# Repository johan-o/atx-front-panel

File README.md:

# atx-front-panel
A simple KiCad project to provide buttons and indicator LEDs for a standard ATX motherboard front header.

## BOM / Parts List

| Count | Part |
| --- | --- |
| 2 | 6x5mm through-hole push buttons |
| 2 | 0805 SMD LEDs |
| 1 | 2x5 2.54 vertical pin header, male | 
| 1 | 2x5 2.54 vertical pin header, female |

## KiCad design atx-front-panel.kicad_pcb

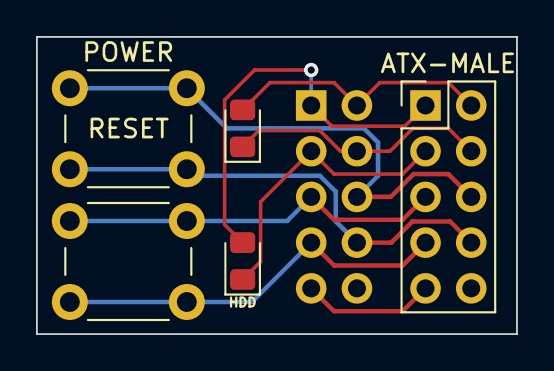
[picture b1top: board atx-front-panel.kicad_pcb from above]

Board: 2 copper layers, 26.7 x 16.5 mm, 6 parts (1 on the bottom side), 9 nets.

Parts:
ATX-FEMALE: Header_02x05_Odd_Even; PinSocket_2x05_P2.54mm_Vertical
ATX-MALE: Conn_02x05_Odd_Even; PinHeader_2x05_P2.54mm_Vertical
DPWR1: LED; LED_0805_2012Metric_Pad1.15x1.40mm_HandSolder
HDD: LED; LED_0805_2012Metric_Pad1.15x1.40mm_HandSolder
POWER: SW_Push; SW_PUSH_6mm_H5mm
RESET: SW_Push; SW_PUSH_6mm_H5mm

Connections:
/HDD_LED+: ATX-FEMALE.1, ATX-MALE.1, HDD.2 (A)
/HDD_LED-: ATX-FEMALE.3, ATX-MALE.3, HDD.1 (K)
/PWR_BUTT1: ATX-FEMALE.6, ATX-MALE.6, POWER.1
/PWR_BUTT2: ATX-FEMALE.8, ATX-MALE.8, POWER.2
/PWR_LED+: ATX-FEMALE.2, ATX-MALE.2, DPWR1.2 (A)
/PWR_LED-: ATX-FEMALE.4, ATX-MALE.4, DPWR1.1 (K)
/RESET_BUTT1: ATX-FEMALE.5, ATX-MALE.5, RESET.1
/RESET_BUTT2: ATX-FEMALE.7, ATX-MALE.7, RESET.2
GND: ATX-FEMALE.9, ATX-MALE.9

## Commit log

2023-08-16 added license
